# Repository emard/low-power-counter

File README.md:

# Low power counter with ATTINY85V

Intended for counting slow pulses which
occur once in few seconds or slower.

Counter keeps its state in EEPROM
which retains data when unpowered 
(without battery).

Counts up to 4 input channels and sends
them over 1 multiplexed output line.

Runs on 3V lithium battery like CR2032.
In standby state it enters low power mode (below 1uA),
what makes a long battery life.

Everything runs on a small AVR ATTINY85V microcontroller,
a single chip in 8-pin package.

# Input and Output

It counts every transition of the input state. It will trigger
on both rising and falling edges. So it will update counter
when input changes from logical 0 to 1 and also back from 1 to 0.

Chip ATTINY85V layout

    nRESET |1  \/  8| +3V
       IN3 |2      7| IN2
       OUT |3      6| IN1
       GND |4      5| IN0

Too fast events >10Hz will not be counted, for example mechanical
contact ringing of the input switch will be filtered out.

After each input pulse, new counter state is sent over
the serial digital line. Output is a timed bit sequence 
containing header, channel number, counter value and CRC.
Output is intended to be connected to a simple
on-off keying (OOK) 433 MHz transmitter and received remotely with
some general-purpose receiver like
[rtl_433](https://github.com/merbanan/rtl_433.git)
(mostly compatible with honeywell.c protocol decoder)
see also
[ArduinoWeatherOS](https://github.com/robwlakes/ArduinoWeatherOS)
about Manchester protocol encoding.

# Power saving issues

When designing the [circuit](/circuit/schematics.pdf) 
take into account that every current flow
draws some power, so for example when internal pull-up resistors
in the chip are enabled, each input connected to GND will draw about 
80uA which can drain CR2032 battery in 3 months.
Option is to disable internal pull-up and connect external
1Mohm pull-up resistor. It will draw 3uA per grounded input pin,
but will also be more sensitive to environmental electric noise.

During 3V battery life, voltage will drop down to about 2V.
Low-voltage version of the chip "ATTINY85V" is recommended
because it is designed to work down to 1.8V.
Normal "ATTINY85" is designed down to 2.7V but it 
seems to work at 2V though.

The output transmitter should also be designed to work with
battery voltage below 2V and have low power mode when idle.
SYN115 433MHZ ASK Transmitter Module works well.

# Todo

    [ ] Reset all counters with nRESET
    [ ] Battery voltage monitoring

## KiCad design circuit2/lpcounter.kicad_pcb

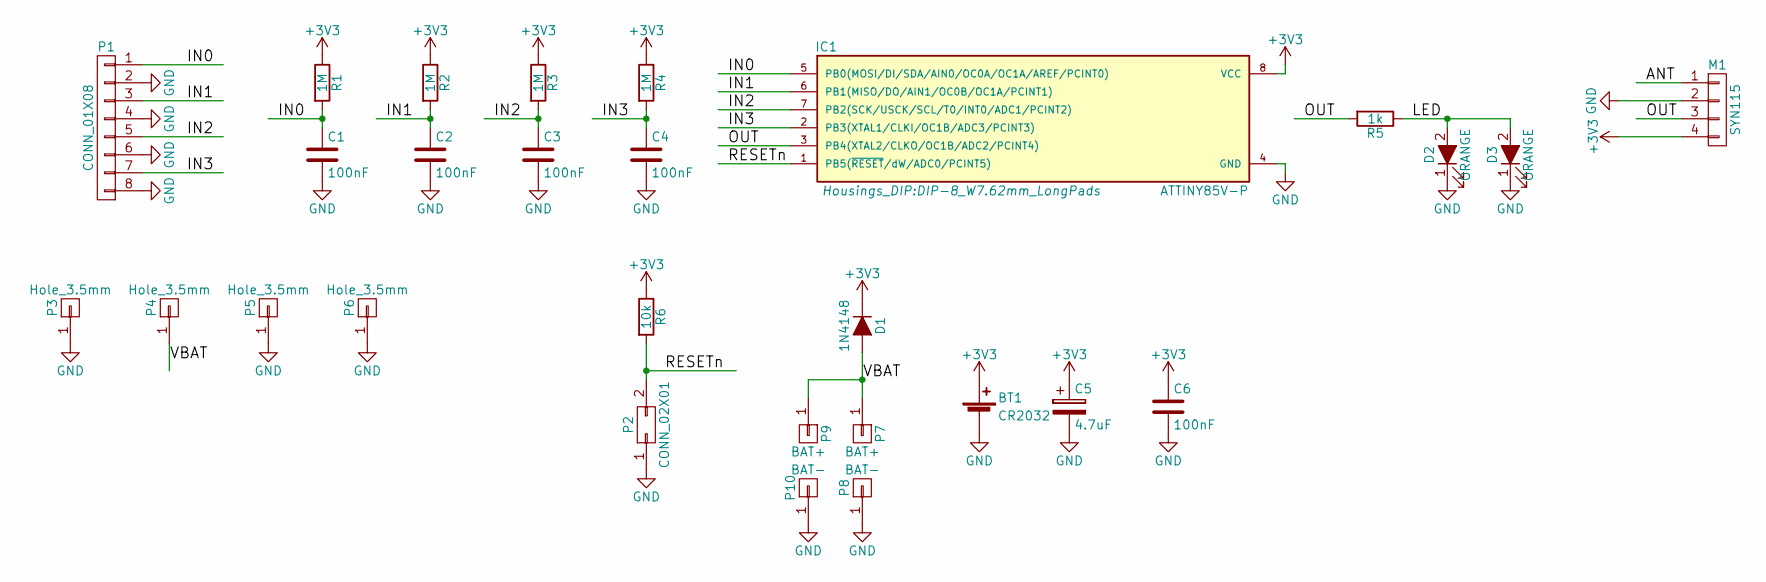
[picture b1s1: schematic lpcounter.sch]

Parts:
BT1: CR2032; Keystone_106_1x20mm-CoinCell
C1, C2, C3, C4, C6: 100nF; C_1206_HandSoldering
C5: 4.7uF; Tantalum_Case-U_EIA-6032-15_Hand
D1: 1N4148; MELF_Handsoldering
D2: ORANGE; LED-5MM
D3: ORANGE; LED_1206
IC1: ATTINY85V-P; DIP-8_W7.62mm_LongPads
M1: SYN115
P1: CONN_01X08; PhoenixContact_MSTBVA-G_08x5.08mm_Vertical
P2: CONN_02X01; Pin_Header_Straight_1x02
P3, P4, P5, P6: Hole_3.5mm; MountingHole_3.5mm_Pad
P7, P9: BAT+; Pin_Header_Straight_1x01
P8, P10: BAT-; Pin_Header_Straight_1x01
R1, R2, R3, R4: 1M; R_1206_HandSoldering
R5: 1k; R_1206_HandSoldering
R6: 10k; R_1206_HandSoldering

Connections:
+3V3: BT1.1 (+), C5.1, C6.1, D1.1 (K), IC1.8 (VCC), M1.4, R1.1, R2.1, R3.1, R4.1, R6.1
/ANT: M1.1
/IN0: C1.1, IC1.5 (PB0(MOSI/DI/SDA/AIN0/OC0A/OC1A/AREF/PCI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), P1.1, R1.2
/IN1: C2.1, IC1.6 (PB1(MISO/DO/AIN1/OC0B/OC1A/PCINT1)), P1.3, R2.2
/IN2: C3.1, IC1.7 (PB2(SCK/USCK/SCL/T0/INT0/ADC1/PCINT2)), P1.5, R3.2
/IN3: C4.1, IC1.2 (PB3(XTAL1/CLKI/OC1B/ADC3/PCINT3)), P1.7, R4.2
/LED: D2.2 (A), D3.2 (A), R5.1
/OUT: IC1.3 (PB4(XTAL2/CLKO/OC1B/ADC2/PCINT4)), M1.3, R5.2
/RESETn: IC1.1 (PB5(~RESET~/dW/ADC0/PCINT5)), P2.2, R6.2
/VBAT: D1.2 (A), P4.1, P7.1, P9.1
GND: BT1.2 (-), C1.2, C2.2, C3.2, C4.2, C5.2, C6.2, D2.1 (K), D3.1 (K), IC1.4 (GND), M1.2, P1.2, P1.4, P1.6, P1.8, P2.1, P3.1, P5.1, P6.1, P8.1, P10.1

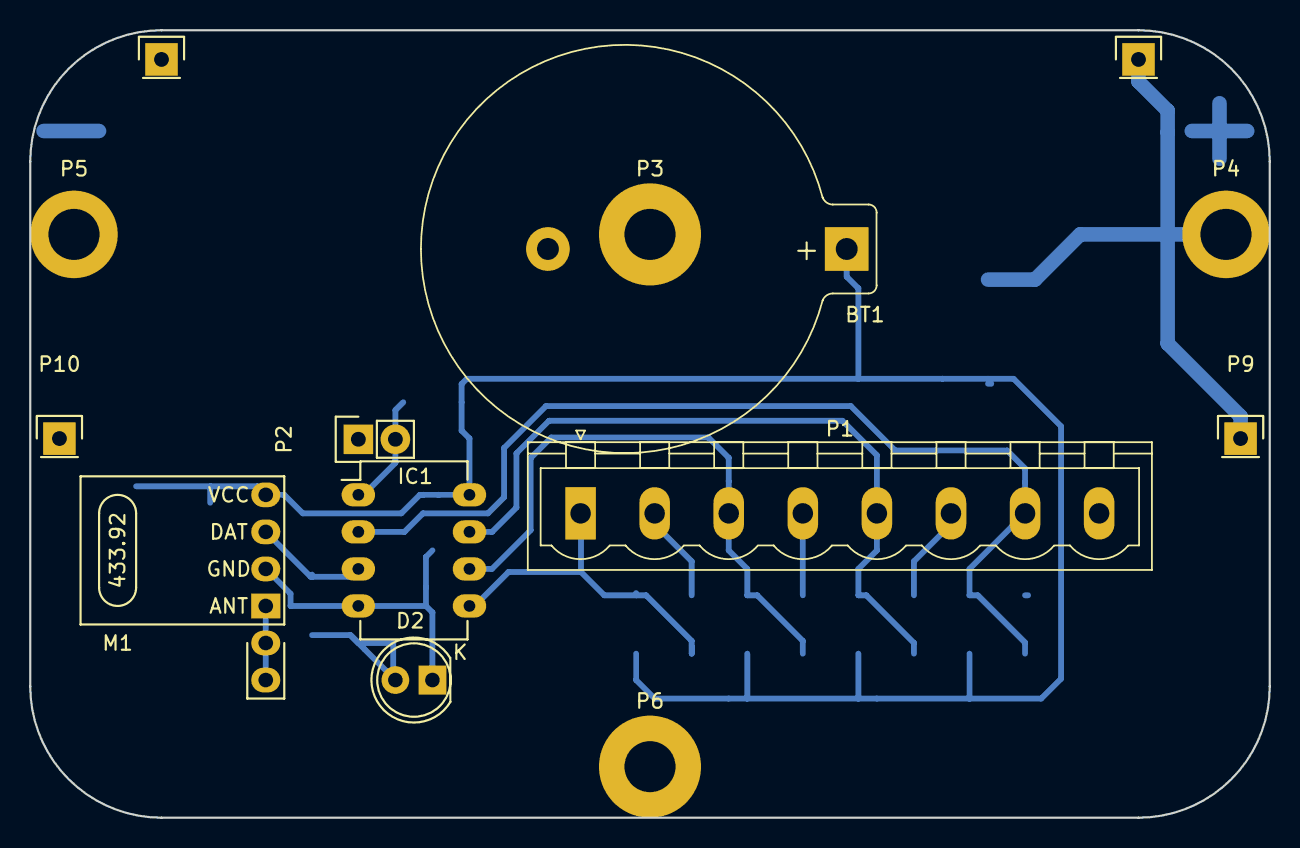
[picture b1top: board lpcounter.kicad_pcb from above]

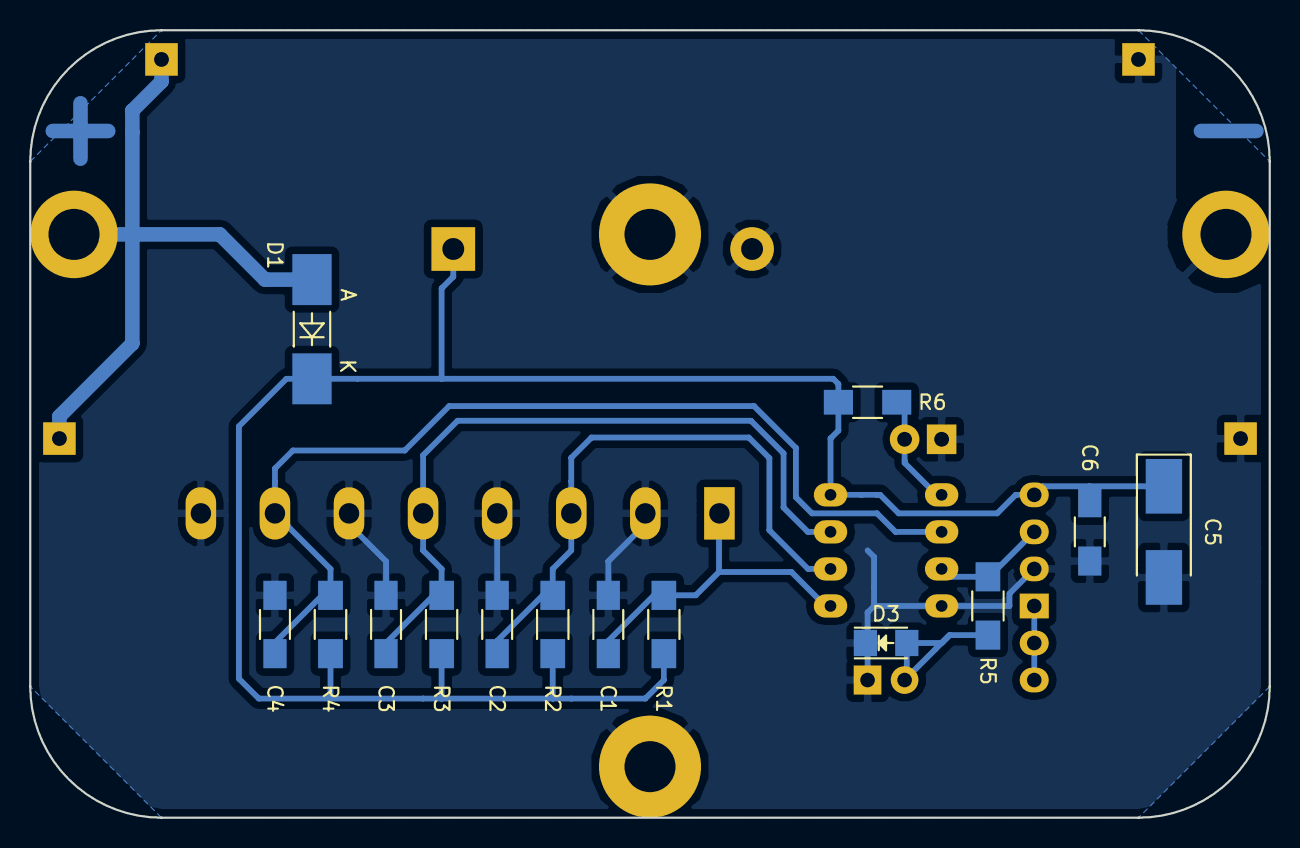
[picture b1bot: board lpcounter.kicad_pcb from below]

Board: 2 copper layers, 85.0 x 54.0 mm, 28 parts (14 on the bottom side), 10 nets.

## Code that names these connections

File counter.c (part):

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#include <avr/sleep.h>
// #include <util/crc16.h>

#define LED (1<<PB4)
#define INPUT ((1<<PB0)|(1<<PB1)|(1<<PB2)|(1<<PB3))
#define PULLUP ((0<<PB0)|(0<<PB1)|(0<<PB2)|(0<<PB3))
#define INTERRUPT_PINS ((1<<PCINT0)|(1<<PCINT1)|(1<<PCINT2)|(1<<PCINT3))

#define ADC_DISABLE() (ADCSRA &= ~(1<<ADEN)) // disable ADC (before sleep)
#define ADC_ENABLE() (ADCSRA |= (1<<ADEN) | (1<<ADATE)) // enable continuous ADC (after sleep)
#define PIN_CHANGE_INTERRUPT_ENABLE() (GIMSK |= (1<<PCIE))
#define PIN_CHANGE_MONITOR(n) (PCMSK = n) // example: use (PCINT2 | PCINT3) to monitor PB2 and PB3 
#define PIN_CHANGE_FLAG_CLEAR() (GIFR = PCIF)

enum 
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
 PIN_CHANGE_FLAG_CLEAR();
 PIN_CHANGE_INTERRUPT_ENABLE();
 PIN_CHANGE_MONITOR(INTERRUPT_PINS); // this is PB0-PB3 inputs
 // should already set monitored pin as input and enable its pull up
 PIN_CHANGE_FLAG_CLEAR();

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
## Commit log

2017-04-24 inital commit
2017-04-24 readme
2017-04-24 untested code that handles eeprom and enters sleep mode
2017-04-24 untested code to wake from sleep at interrupt
2017-04-24 empty pin change interrupt service routine
2017-04-24 separate makefile for attiny84 and attiny85
2017-04-24 getting it to compile and upload to device
2017-04-24 It constantly blinks, no sleep mode? Add forever loop to check this
2017-04-24 it constantly awakens from sleep mode
2017-04-24 eeprom writes something at 1st location but doesn't advance to next record
2017-04-24 fixing finding 0-record
2017-04-24 counter eeprom seems to count now
2017-04-24 device now enters power down mode, draws around 1uA
2017-04-24 pin change interrupt works on PB0 only
2017-04-25 clean up wakeup on PB0
2017-04-25 works on PB3 now
2017-04-25 OK, pin change wakeup seems to work. Note that weak pullup when enabled and pin held down will consume 80uA
2017-04-25 small code cleanup
2017-04-25 ISR is actually not needed, input switch monitoring will be slow
2017-04-25 it counts, it blinks
2017-04-25 4 inputs but not yet tracking them
2017-04-25 tracking each pin, but unreliable
2017-04-25 something works, something doesnt
2017-04-25 untested attempt to use ISR to track pin change
2017-04-25 unsupported use of timer overflow to precisely time output transmit sequence
2017-04-25 use prescaler 1024
2017-04-25 good input pulse detection timer not working
2017-04-25 timer seems to work now, missing 1<<
2017-04-25 enabling and slightly bugfixing code for interrupt pin state tracking and counting
2017-04-25 use 64-bit value to send header, counter and CRC.
2017-04-26 readme update
2017-04-26 untested clearing of the eeprom on external reset
2017-04-26 makefile: udev rule for avr-doper in comment
2017-04-26 disabling erase counter after reset - it erases counter on every power up
2017-04-26 code cleanup
2017-04-27 detect pin change during power off
2017-04-27 untested manchester encoding
2017-04-27 packet union for transmission, filled with some dummy data
2017-04-28 updated manchester encoding, crc calculation, all untested
2017-04-28 trying to improve speed of counting, counter loop will accumulate changes when pulses come one after another, taking de-bounce delay into account. When pulses stop coming within some delay time, it w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
2017-04-28 speeding up the timer
2017-04-28 more precise timing, still 0 and 1 are of different width
2017-04-28 better transmit code: symmetric on/off pulse
2017-04-28 retransmit the packed, small code cleanup
2017-04-28 encode channel number (0-3)
2017-04-29 encoding channel numer in 'unknown' field small code cleanup
2017-04-29 prolong wakeup pulse to 200us and shorten retransmit pause to 15 ms
2017-04-29 delay() bugfixed to work with 16-bit paramter
2017-04-29 make counter directly readable as serial number, debounce time as config parameter
2017-04-29 Issue wakeup pulse only before first transmission. Disable interrupt during transmit() to improve bit timing.
2017-04-29 makefile: add backslash on flash/verify avrdude line
2017-04-29 initial setting of counter values after reflashing
2017-04-29 configure pullup resistors for each input pin
2017-04-29 readme update, count frequency about 10Hz
2017-04-29 readme update, manchester
2017-04-30 readme update, sume power saving tips
2017-05-01 retransmit: option to alternate between 2 different delay times. Default 50 retransmissions, attempt to improve the range.
2017-05-02 readme update, need to monitor battery voltage
2017-05-02 battery voltage monitoring and reporting - untested
2017-05-02 fix ADC setting to measure battery voltage
2017-05-02 comments on how to calculate battery voltage
2017-05-02 comment approx battery values
2017-05-02 free running ADC
2017-05-02 clear ADCSRB register for ADC free-running
2017-05-02 Simple python logger that parses output from rtl_433 stores it to mysql database and calls shell command with audible notification for each pulse received
2017-05-08 Schematics and rough PCB in KiCAD
2017-05-08 proper battery holder for CR2032
2017-05-08 readme: link to schematics PDF
2017-05-08 schematics PDF
2017-05-08 updating PCB
2017-05-08 fully routed
2017-05-08 small chamges, optimizing routes
2017-05-09 correct footprint for SYN115, 4 screw holes, optimizing PCB drawing 18650 battery outiline
2017-05-09 3V battery connected direct, 3.7V battery connect in series with diode 1N4147
2017-05-09 Helper files to notify and report from asterisk
2017-05-09 extensions.conf: comments update
2017-05-10 placeholder for both SMD and TH LED
2017-05-11 drawing ABC plastic box and 18650 battery footprint for possible PCB which fits in such box
2017-05-13 another PCB, same circuit but fit into ABC box
2017-05-13 optimizing PCB
2017-05-13 changing pushbutton to jumper
2017-05-13 increase PCB to fully fit into ABC box, multiple battery contacts
2017-05-15 increase clearance in design rules
2017-05-15 preparation for fabrication moving electronic parts away from the edge
2017-05-15 holes update
2017-05-15 update gerbers
2017-05-16 small PCB optimizations, moving screw connector away from CR2032 battery add top zone layer and capacitor on top
2017-06-18 removing weak pullups form all inputs. Larger pullup (1M) is externally mounted on PCB
